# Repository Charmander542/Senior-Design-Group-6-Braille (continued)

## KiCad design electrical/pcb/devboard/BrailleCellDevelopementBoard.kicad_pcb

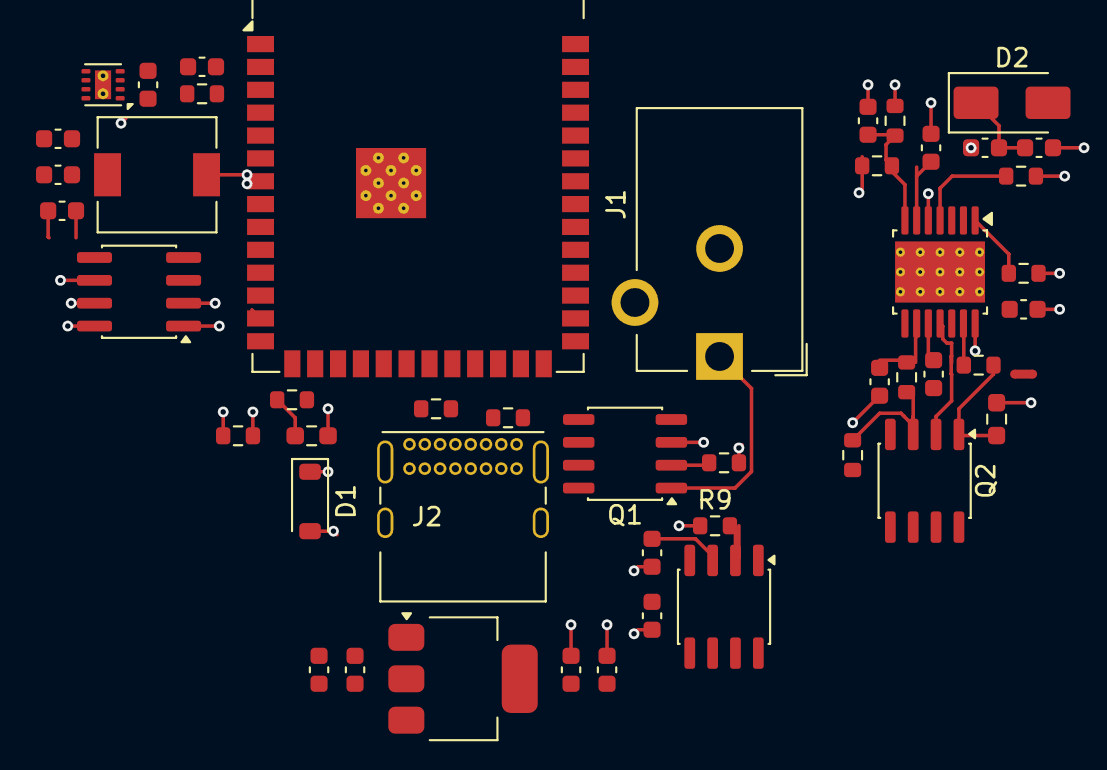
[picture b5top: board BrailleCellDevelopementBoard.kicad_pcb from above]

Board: 4 copper layers, 48 parts (0 on the bottom side), 33 nets.

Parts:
C1: 4uF; C_0603_1608Metric
C2: 1.2uF; C_0603_1608Metric
C3: 47pF; C_0603_1608Metric
C7: CIN; C_0603_1608Metric
C10, C11, C12, C13, C14: C; C_0603_1608Metric
C15, C17: 10uF; C_0603_1608Metric
C16, C18, C20: 0.1uF; C_0603_1608Metric
C19: 22uF; C_0603_1608Metric
Chf1: 120pF; C_0603_1608Metric
Css1: 100nF; C_0603_1608Metric
Cvcc1: 1uF; C_0603_1608Metric
D1: D_Zener; D_SOD-123
D2: 500mV; D_SMA
J1: Barrel_Jack; BarrelJack_CUI_PJ-102AH_Horizontal
J2: USB_C_Receptacle_USB2.0_14P; USB_C_Receptacle_GCT_USB4085
L2: 2.2uH; L_6.3x6.3_H3
NT1: NetTie_2; NetTie-2_SMD_Pad0.5mm
Q1, Q2: NMOS; SO-8_3.9x4.9mm_P1.27mm
Q3: PMOS; SO-8_3.9x4.9mm_P1.27mm
R1, R8: R; R_0603_1608Metric
R2: 100Ω; R_0603_1608Metric
R3: 360kΩ; R_0603_1608Metric
R4: 10kΩ; R_0603_1608Metric
R5, R6: RCOMP; R_0603_1608Metric
R9: 100K; R_0603_1608Metric
R10, R11: 5.1k; R_0603_1608Metric
R12: 10k; R_0603_1608Metric
R13: R_Shunt; R_0603_1608Metric
Rcs1: 0.1Ω; R_0603_1608Metric
Rtop1: 200kΩ; R_0603_1608Metric
T1: Transformer_1P_1S; R_0603_1608Metric_Pad0.98x0.95mm_HandSolder
TH1: Thermistor_NTC; R_0603_1608Metric_Pad0.98x0.95mm_HandSolder
U2: ESP32-S3-WROOM-1
U3: AMS1117-3.3; SOT-223-3_TabPin2
U4: TPS62162DSG; WSON-8-1EP_2x2mm_P0.5mm_EP0.9x1.6mm_ThermalVias
U5: INA219AxD; SOIC-8_3.9x4.9mm_P1.27mm
U6: LM5185QPWPRQ1; Texas_HTSSOP-14-1EP_4.4x5mm_P0.65mm_EP3.4x5mm_Mask3.155x3.2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

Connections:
+3.3V: C13.1, C14.1, U3.2 (VO)
+5V: C11.1, C12.1, C16.1, C17.1, C18.2, Q3.1 (D), U3.3 (VI), U4.3 (EN)
+24V: C3.2, C7.1, Chf1.2, Css1.2, D1.1 (K), NT1.2, Q1.3 (S), R4.1, R5.2, R6.2, R9.1, R13.1, R13.2, Rtop1.1, T1.1 (AA), U5.7 (IN-), U5.8 (IN+), U6.5 (AGND), U6.14 (VIN), U6.15 (EP)
/MCU/3V3: R8.1, U2.2 (3V3)
/MCU/USB_DM: J2.A7 (D-), J2.B7 (D-), U2.13 (USB_D-)
/MCU/USB_DP: J2.A6 (D+), J2.B6 (D+), U2.14 (USB_D+)
/PowerSystem/+3V3: R12.1, U5.5 (VS)
/PowerSystem/+450V: C1.1, C2.1, D2.1 (K)
/PowerSystem/TEMP_VAL: R12.2, TH1.2
CHIP_PU: C10.1, R8.2, U2.3 (EN)
COMP: Chf1.1, R5.1, R6.1, U6.7 (COMP)
GND: C1.2, C2.2, C10.2, C11.2, C12.2, C13.2, C14.2, C15.2, C16.2, C17.2, C19.1, C19.2, C20.1, C20.2, D1.2 (A), J1.2, J2.A1 (GND), J2.A12 (GND), J2.B1 (GND), J2.B12 (GND), L2.2, R1.2, R10.2, R11.2, TH1.1, U3.1 (GND), U4.4 (AGND), U4.5 (FB), U4.6 (VOS), U5.1 (A1), U5.2 (A0), U5.6 (GND)
GNDPWR: C7.2, Cvcc1.2, NT1.1, Rcs1.1, U6.8 (PGND)
unnamed: J2.A5 (CC1), R11.1
unnamed: J2.B5 (CC2), R10.1
unnamed: J1.1, Q1.1 (D)
unnamed: Q1.2 (G), R1.1
unnamed: Q2.1 (D), R3.2, T1.2 (AB)
unnamed: Q2.2 (G), U6.11 (GATE)
unnamed: Q2.3 (S), R2.2, Rcs1.2
unnamed: Q3.2 (G), R9.2
unnamed: C15.1, J2.A4 (VBUS), J2.A9 (VBUS), J2.B4 (VBUS), J2.B9 (VBUS), Q3.3 (S)
unnamed: U2.1 (GND), U2.40 (GND), U2.41 (GND)
unnamed: L2.1, U4.7 (SW)
unnamed: C18.1, U4.2 (VIN)
unnamed: C3.1, R2.1, U6.9 (CS)
unnamed: Rtop1.2, U6.1 (EN)
unnamed: R3.1, U6.13 (FB)
unnamed: R4.2, U6.4 (RSET)
unnamed: Css1.1, U6.6 (SS)
unnamed: Cvcc1.1, U6.10 (VCC)
SCL: U2.11 (IO18), U5.4 (SCL)
SDA: U2.10 (IO17), U5.3 (SDA)

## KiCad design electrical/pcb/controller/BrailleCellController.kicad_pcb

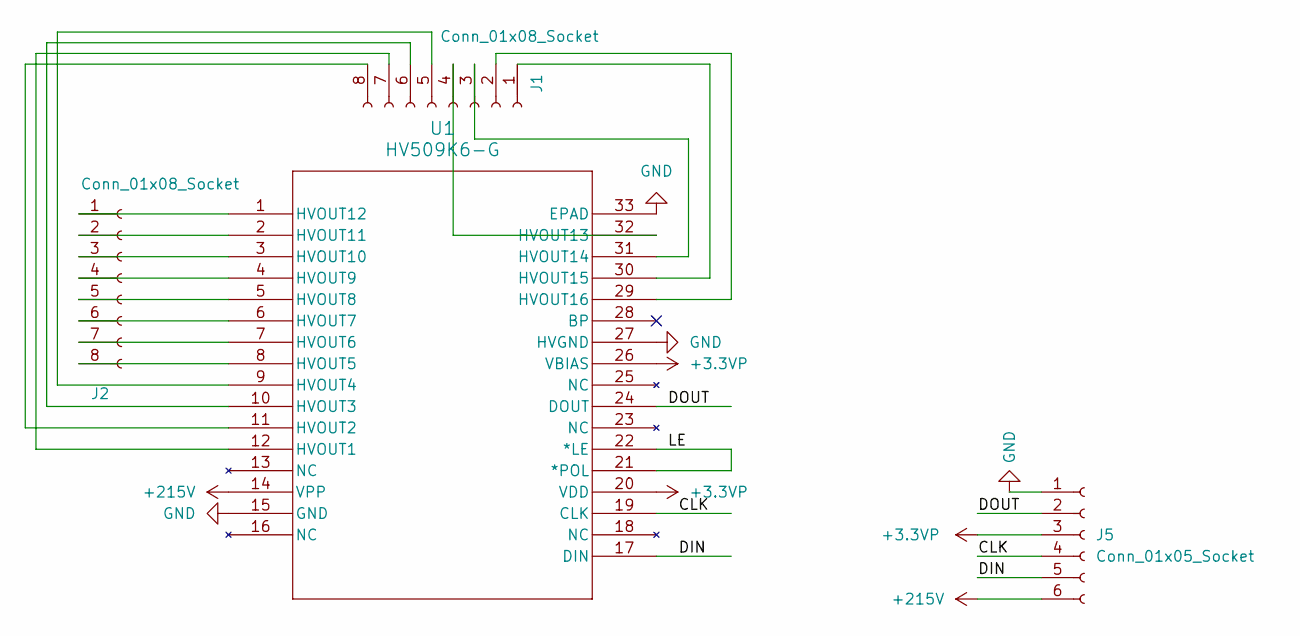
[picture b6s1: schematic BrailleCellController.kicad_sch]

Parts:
J1, J2: Conn_01x08_Socket; FPC Connecotr
J5: Conn_01x05_Socket; PinHeader_1x06_P1.00mm_Vertical
U1: HV509K6-G; QFN32_5X5MC_MCH

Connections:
+3.3VP: J5.3, U1.20 (VDD), U1.26 (VBIAS)
+215V: J5.6, U1.14 (VPP)
/CLK: J5.4, U1.19 (CLK)
/DIN: J5.5, U1.17 (DIN)
/DOUT: J5.2, U1.24 (DOUT)
/LE: U1.21 (*POL), U1.22 (*LE)
GND: J5.1, U1.15 (GND), U1.27 (HVGND), U1.33 (EPAD)
unnamed: J1.1, U1.30 (HVOUT15)
unnamed: J1.2, U1.29 (HVOUT16)
unnamed: J1.3, U1.31 (HVOUT14)
unnamed: J1.4, U1.32 (HVOUT13)
unnamed: J1.5, U1.9 (HVOUT4)
unnamed: J1.6, U1.10 (HVOUT3)
unnamed: J1.7, U1.12 (HVOUT1)
unnamed: J1.8, U1.11 (HVOUT2)
unnamed: J2.1, U1.1 (HVOUT12)
unnamed: J2.2, U1.2 (HVOUT11)
unnamed: J2.3, U1.3 (HVOUT10)
unnamed: J2.4, U1.4 (HVOUT9)
unnamed: J2.5, U1.5 (HVOUT8)
unnamed: J2.6, U1.6 (HVOUT7)
unnamed: J2.7, U1.7 (HVOUT6)
unnamed: J2.8, U1.8 (HVOUT5)

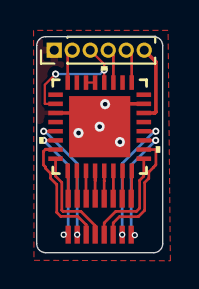
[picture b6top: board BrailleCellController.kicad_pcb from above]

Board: 2 copper layers, 7.0 x 12.0 mm, 4 parts (0 on the bottom side), 23 nets.

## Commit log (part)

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2025-09-23 Power System
2025-09-25 minor stuff
2025-10-01 cell shifter routed
2025-10-01 Revert "Delete electrical directory for better gitignore"
    This reverts commit 181b4a21364ede14b701790e8bdf27dabea5567c.
2025-10-01 gitignore
2025-10-01 Revert "Delete electrical directory"
    This reverts commit 27c4fd279335de581d558488b3912bec10442990.
2025-10-01 ignore bad files
2025-11-05 first round for component testing
2025-11-06 first edits for code
2025-11-06 inital code changes
2025-11-14 library fix
2025-11-16 added converting library
2025-11-17 modified library to arduino core library
2025-11-17 removed unnecessary documentation
2025-11-18 Update BrailleConverter.cpp
    modified to be able to fit in the arduino uno
2025-11-18 Update BrailleConverter.h
    edited to allow for fitting into arduino uno
2025-11-18 Create brailledemo
    serial to control signal IO with full braille conversion for arduino uno
2025-12-08 some more chages
2026-02-10 Add OCR functionality and UI buttons for OCR
2026-03-04 Implement open and save text file features
    Added functionality to open and save text files in the application, including UTF-8 BOM handling.
2026-03-06 Add files via upload
    flyback and mosfet
2026-03-07 schematic done
2026-03-07 started layout
2026-03-19 Add braille project files
    Include tools (serial_braille, braille converter, pdf/doc to braille),
    PlatformIO firmware (src, lib), wokwi simulation files, and project config.
    Made-with: Cursor
2026-03-23 layout in (1)
2026-03-31 ECE day demo board added
2026-03-31 Enhance Python integration and file dialog filters
    Updated file filters for open dialog and improved Python integration for Arduino connection. Enhanced error handling and added Python document extraction functionality.
2026-03-31 Updated layout and board shape determined
2026-04-03 placement done
2026-04-05 initial layout of dev
2026-04-05 Add shorthand Braille conversion helpers
    This file provides functions to convert text into shorthand Braille, including common contractions and formatting for terminal output.
2026-04-05 Add desktop UI for document-to-Braille conversion
    This file implements a desktop UI for converting documents to Braille, featuring an Open/Save/Edit/Convert flow. It connects to existing extraction and Braille conversion systems.
2026-04-07 Add to_shorthand_patterns function
    Implement function to convert text to shorthand Braille cell patterns.
2026-04-09 esp32 wifi conversion
2026-04-10 layout finished
2026-04-11 led board
2026-04-12 Enhance driver with shorthand and PDF support
    Added support for shorthand braille and PDF text extraction.
2026-04-17 ordered boards
2026-04-23 chnages for updating firmware for shift register
2026-04-25 Update BrailleCell.h
    added OE pin and Clear pin. Also changed mentions of 8 dots to 6 because we are demoing on 6 dots
2026-04-27 Add queued multi-user send flow for phone web UI.
    This updates the Flask and frontend flow to process submissions in FIFO order with live queue visibility, and adds a runbook/test checklist to finalize deployment verification.
    Made-with: Cursor
2026-05-01 Changed it to display two letters at a time
2026-05-01 one letter
